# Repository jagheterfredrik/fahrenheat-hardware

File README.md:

# fahrenheat-hardware

A hat for the ESP32-C3 SuperMini that adds CAN-FD and 12 V input. [Firmware](https://github.com/jagheterfredrik/fahrenheat) written on Zephyr.

- **CAN:** MCP251863 (CAN FD controller + transceiver) over SPI
- **Power:** TPS5430 buck, VCC in → 5 V to the SuperMini
- **CN1:** 3.81 mm terminal — VCC, GND, CANL, CANH

## Ordering

All parts carry LCSC numbers. `python3 export_jlcpcb.py` writes gerbers, BOM and CPL to `jlcpcb/` for JLCPCB assembly.

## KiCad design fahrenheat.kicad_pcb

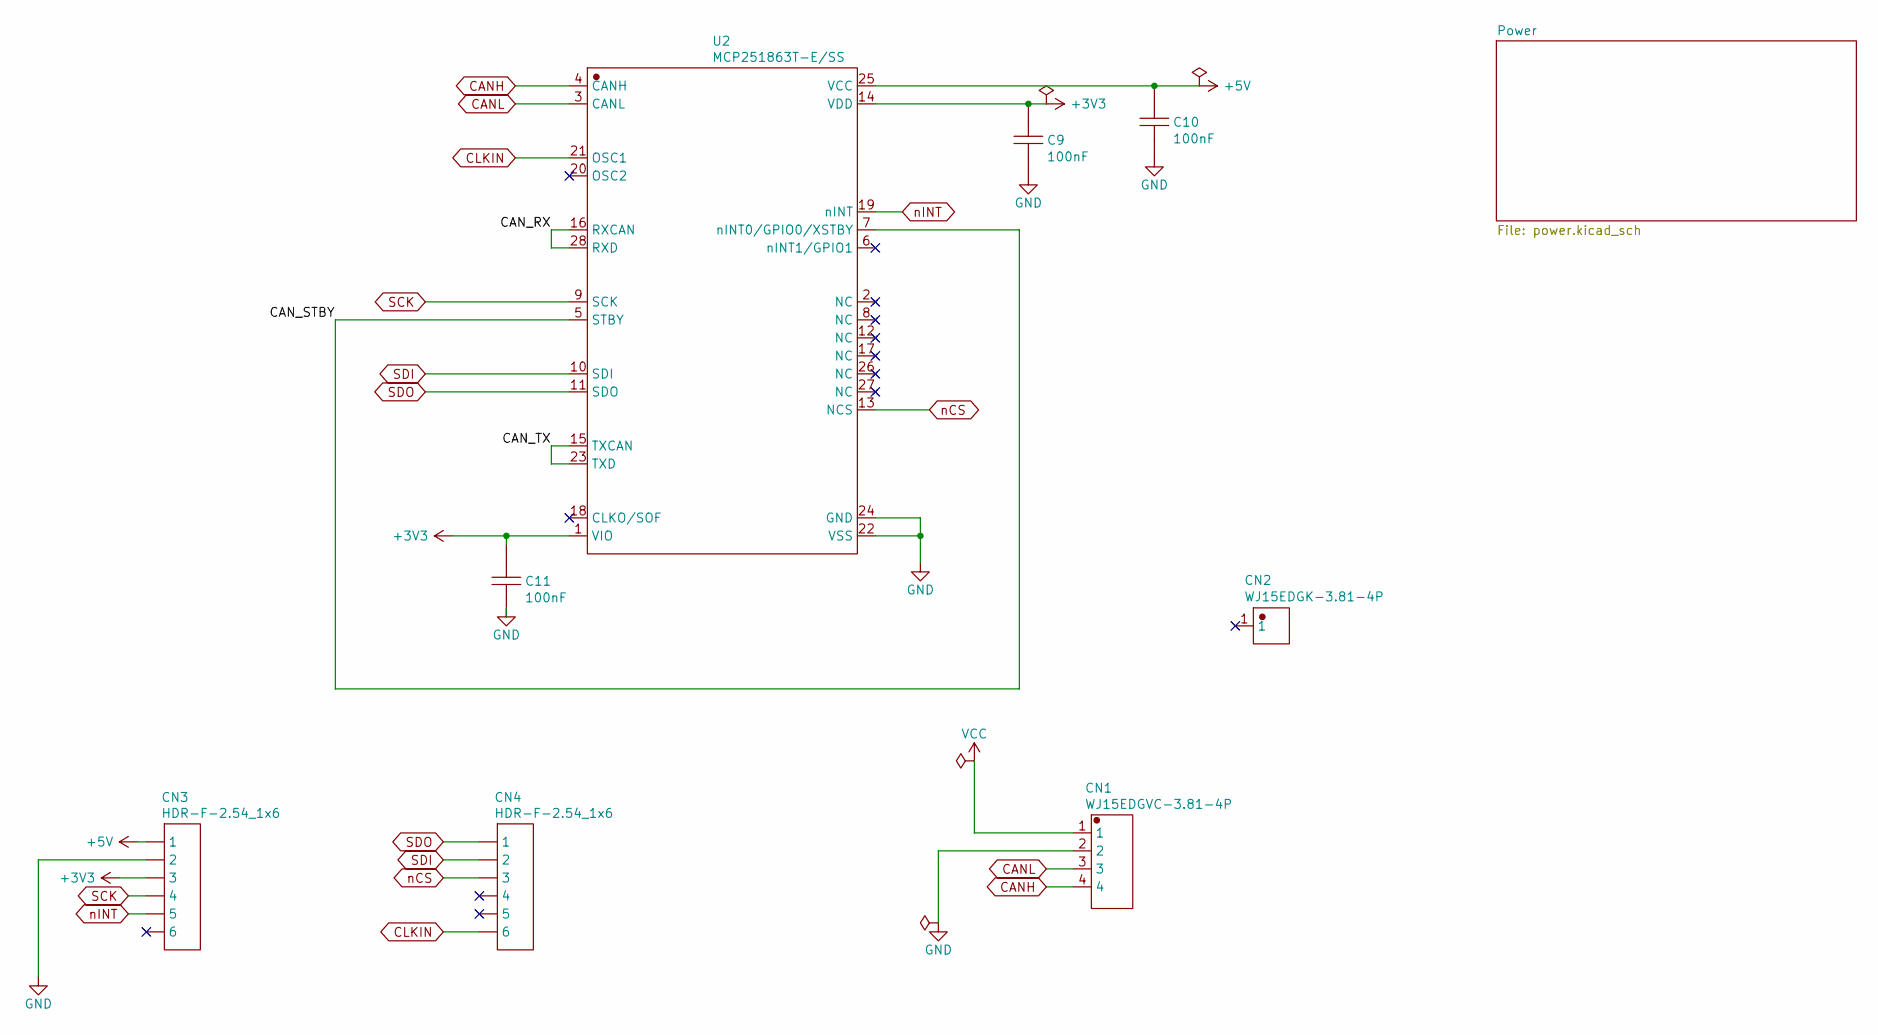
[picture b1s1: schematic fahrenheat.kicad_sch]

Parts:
C9, C10, C11: 100nF; C0402; MPN CL05B104KO5NNNC; LCSC C1525
CN1: WJ15EDGVC-3.81-4P; CONN-TH_4P-P3.81_WJ2EDGVC-3.81-4P; MPN WJ15EDGVC-3.81-4P; LCSC C8410
CN2: WJ15EDGK-3.81-4P; MPN WJ15EDGK-3.81-4P; LCSC C7244
CN3, CN4: HDR-F-2.54_1x6; HDR-F-2.54_1X6; LCSC C40877
U2: MCP251863T-E/SS; SSOP-28_L10.2-W5.3-P0.65-LS7.8-BL; MPN MCP251863T-E/SS; LCSC C5226885

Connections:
+3V3: C9.2, C11.2, CN3.3, U2.1 (VIO), U2.14 (VDD)
+5V: C10.2, CN3.1, U2.25 (VCC); also elsewhere on the board
/MCU_CAN/CAN_RX: U2.16 (RXCAN), U2.28 (RXD)
/MCU_CAN/CAN_STBY: U2.5 (STBY), U2.7 (nINT0/GPIO0/XSTBY)
/MCU_CAN/CAN_TX: U2.15 (TXCAN), U2.23 (TXD)
CANH: CN1.4, U2.4 (CANH)
CANL: CN1.3, U2.3 (CANL)
CLKIN: CN4.6, U2.21 (OSC1)
GND: C9.1, C10.1, C11.1, CN1.2, CN3.2, U2.22 (VSS), U2.24 (GND); also elsewhere on the board
SCK: CN3.4, U2.9 (SCK)
SDI: CN4.2, U2.10 (SDI)
SDO: CN4.1, U2.11 (SDO)
VCC: CN1.1; also elsewhere on the board
nCS: CN4.3, U2.13 (NCS)
nINT: CN3.5, U2.19 (nINT)

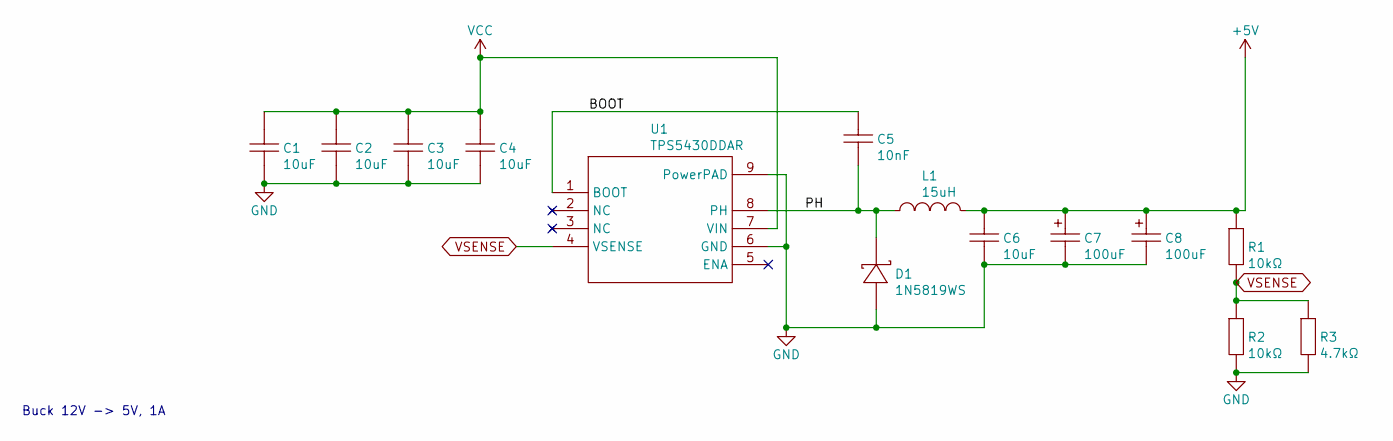
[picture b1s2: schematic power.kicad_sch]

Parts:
C1, C2, C3, C4: 10uF; C0603; MPN CL10A106MA8NRNC; LCSC C96446
C5: 10nF; C0402_LongPad; MPN CL05B103KB5NNNC; LCSC C15195
C6: 10uF; C0402_LongPad; MPN CL05A106MQ5NUNC; LCSC C15525
C7, C8: 100uF; CASE-B_3528; MPN TAJB107K006RNJ; LCSC C16133
D1: 1N5819WS; SOD-323_L1.8-W1.3-LS2.5-RD; MPN 1N5819WS; LCSC C191023
L1: 15uH; IND-SMD_L4.0-W4.0; MPN FHD4020S-150MT; LCSC C602033
R1, R2: 10kΩ; R0402; MPN 0402WGF1002TCE; LCSC C25744
R3: 4.7kΩ; R0402; MPN 0402WGF4701TCE; LCSC C25900
U1: TPS5430DDAR; ESOP-8_L4.9-W3.9-P1.27-LS6.0-TL-EP; MPN TPS5430DDAR; LCSC C9864

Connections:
+5V: C6.2, C7.1, C8.1, L1.2, R1.2; also elsewhere on the board
/Power/BOOT: C5.2, U1.1 (BOOT)
/Power/PH: C5.1, D1.1, L1.1, U1.8 (PH)
GND: C1.1, C2.1, C3.1, C4.1, C6.1, C7.2, C8.2, D1.2, R2.1, R3.1, U1.6 (GND), U1.9 (PowerPAD); also elsewhere on the board
VCC: C1.2, C2.2, C3.2, C4.2, U1.7 (VIN); also elsewhere on the board
VSENSE: R1.1, R2.2, R3.2, U1.4 (VSENSE)

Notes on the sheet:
Buck 12V -> 5V, 1A

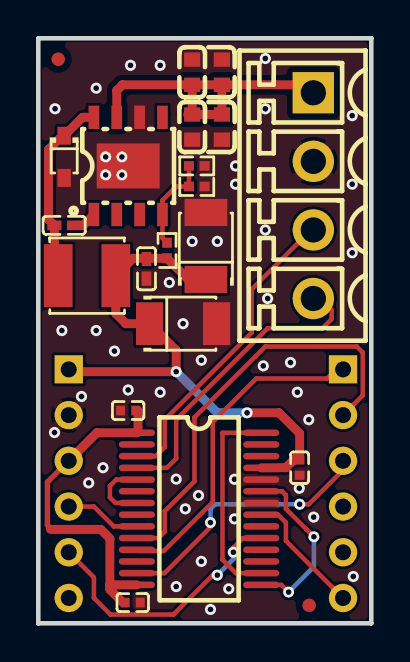
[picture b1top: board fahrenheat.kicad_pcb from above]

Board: 2 copper layers, 18.5 x 32.5 mm, 23 parts (0 on the bottom side), 18 nets.

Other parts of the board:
FID1, FID2: Fiducial_0.75mm_Mask1.5mm
